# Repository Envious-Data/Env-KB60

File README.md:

# Env-KB60
 Another Raspberry Pi Pico Keyboard but this time 60% and compact!

## This project is sort of on hold kinda.

### What Dis!?

This is another Raspberry pi Pico keyboard that ive designed, its a 60% this time around and the diodes are a bit more akin to a normal keyboard, This should support ansi and ISO.
As of right now there are no mount holes nor SVGs for Laser cut acrylic, same for there being no keymap but those arent hard to make for KMK.

to add since my income is relatively low these extra boards ive made may be slow going to make progress since getting PCBs Made and acrylic made costs money which I dont have much of (basically paying bills are more important), With that said I'll happily help if you want work on your own boards of make changes to this one.

### Goal
the goal of this keyboard is to make it GH60 case compatible and a secondary objective is ANSI support.

### Extra notes
in the schematic there are double positions for some keys just to allow for ansi support since I design natively ISO first, there is also 2 backslash keys one of which can be ignored if you use ANSI or ISO.

the rpi pico will need a spacer of some sort so you'll likely just need normal male headers and snip the extra length off once you've soldered the pico to the PCB, DO NOTE that you should do this AFTER installing the switches unless you have a way of removing the rpi pico.

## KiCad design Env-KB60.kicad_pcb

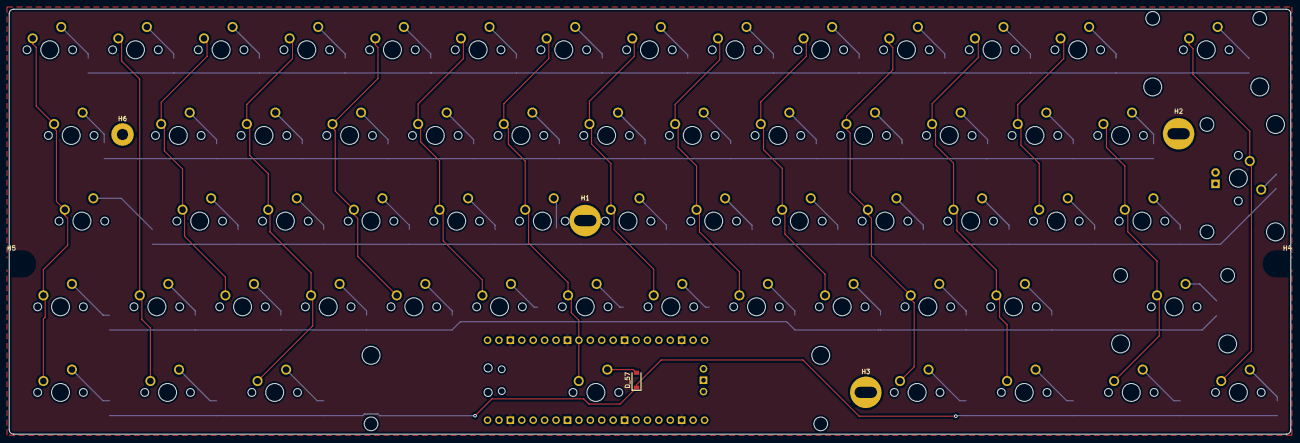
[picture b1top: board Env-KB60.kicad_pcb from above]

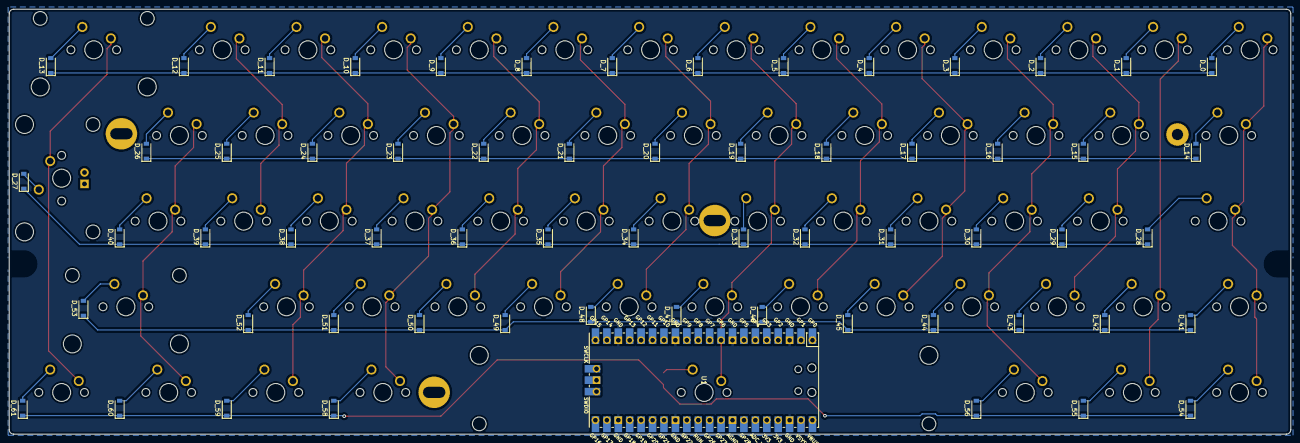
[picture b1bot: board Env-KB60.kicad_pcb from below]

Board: 2 copper layers, 285.0 x 94.5 mm, 131 parts (62 on the bottom side), 83 nets.

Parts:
D_0, D_1, D_2, D_3, D_4, D_5, D_6, D_7, D_8, D_9, D_10, D_11, D_12, D_13, D_14, D_15, D_16, D_17, D_18, D_19, D_20, D_21, D_22, D_23, D_24, D_25, D_26, D_27, D_28, D_29, D_30, D_31, D_32, D_33, D_34, D_35, D_36, D_37, D_38, D_39, D_40, D_41, D_42, D_43, D_44, D_45, D_46, D_47, D_48, D_49, D_50, D_51, D_52, D_53, D_54, D_55, D_56, D_57, D_58, D_59, D_60, D_61: D; D_SOD-123
H1, H2, H3, H4, H5, H6: MountingHole; MountingHole_2.5mm
K_0, K_1, K_2, K_3, K_4, K_5, K_6, K_7, K_8, K_9, K_10, K_11, K_12, K_15, K_16, K_17, K_18, K_19, K_20, K_21, K_22, K_23, K_24, K_25, K_26, K_29, K_30, K_31, K_32, K_33, K_34, K_35, K_36, K_37, K_38, K_39, K_40, K_42, K_43, K_44, K_45, K_46, K_47, K_48, K_49, K_50, K_51, K_52: KEYSW; MXOnly-1U-NoLED
K_13: KEYSW; MXOnly-2U-NoLED
K_14: KEYSW; MXOnly-1.5U-NoLED
K_27: KEYSW; MXOnly-ISO-ROTATED
K_28: KEYSW; MXOnly-1.75U-NoLED
K_41, K_54, K_55, K_56, K_58, K_59, K_60, K_61: KEYSW; MXOnly-1.25U-NoLED
K_53: KEYSW; MXOnly-2.75U-NoLED
K_57: KEYSW; MXOnly-6.25U-ReversedStabilizers-NoLED
U1: Pico; RPi_Pico_SMD_TH

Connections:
GND: U1.3, U1.8, U1.13, U1.18, U1.23, U1.28, U1.38
unnamed: D_0.2, K_0.2
unnamed: D_1.2, K_1.2
unnamed: D_2.2, K_2.2
unnamed: D_3.2, K_3.2
unnamed: D_4.2, K_4.2
unnamed: D_5.2, K_5.2
unnamed: D_6.2, K_6.2
unnamed: D_7.2, K_7.2
unnamed: D_8.2, K_8.2
unnamed: D_9.2, K_9.2
unnamed: D_10.2, K_10.2
unnamed: D_11.2, K_11.2
unnamed: D_12.2, K_12.2
unnamed: D_13.2, K_13.2
unnamed: D_14.2, K_14.2
unnamed: D_15.2, K_15.2
unnamed: D_16.2, K_16.2
unnamed: D_17.2, K_17.2
unnamed: D_18.2, K_18.2
unnamed: D_19.2, K_19.2
unnamed: D_20.2, K_20.2
unnamed: D_21.2, K_21.2
unnamed: D_22.2, K_22.2
unnamed: D_23.2, K_23.2
unnamed: D_24.2, K_24.2
unnamed: D_25.2, K_25.2
unnamed: D_26.2, K_26.2
unnamed: D_27.2, K_27.2
unnamed: D_28.2, K_28.2
unnamed: D_29.2, K_29.2
unnamed: D_30.2, K_30.2
unnamed: D_31.2, K_31.2
unnamed: D_32.2, K_32.2
unnamed: D_33.2, K_33.2
unnamed: D_34.2, K_34.2
unnamed: D_35.2, K_35.2
unnamed: D_36.2, K_36.2
unnamed: D_37.2, K_37.2
unnamed: D_38.2, K_38.2
unnamed: D_39.2, K_39.2
unnamed: D_40.2, K_40.2
unnamed: D_41.2, K_41.2
unnamed: D_42.2, K_42.2
unnamed: D_43.2, K_43.2
unnamed: D_44.2, K_44.2
unnamed: D_45.2, K_45.2
unnamed: D_46.2, K_46.2
unnamed: D_47.2, K_47.2
unnamed: D_48.2, K_48.2
unnamed: D_49.2, K_49.2
unnamed: D_50.2, K_50.2
unnamed: D_51.2, K_51.2
unnamed: D_52.2, K_52.2
unnamed: D_53.2, K_53.2
unnamed: D_54.2, K_54.2
unnamed: D_55.2, K_55.2
unnamed: D_56.2, K_56.2
unnamed: D_57.2, K_57.2
unnamed: D_58.2, K_58.2
unnamed: D_59.2, K_59.2
unnamed: D_60.2, K_60.2
unnamed: D_61.2, K_61.2
col0: K_0.1, K_14.1, K_28.1, K_41.1, K_54.1
col1: K_1.1, K_42.1, K_55.1
col2: K_2.1, K_15.1, K_29.1, K_43.1
col3: K_3.1, K_16.1, K_30.1, K_44.1, K_56.1
col4: K_4.1, K_17.1, K_31.1, K_45.1
col5: K_5.1, K_18.1, K_32.1, K_46.1
col6: K_6.1, K_19.1, K_33.1, K_47.1, K_57.1
col7: K_7.1, K_20.1, K_34.1, K_48.1
col8: K_8.1, K_21.1, K_35.1, K_49.1
col9: K_9.1, K_22.1, K_36.1, K_50.1
col10: K_10.1, K_23.1, K_37.1, K_51.1, K_58.1
col11: K_11.1, K_24.1, K_38.1, K_52.1, K_59.1
col12: K_12.1, K_25.1, K_39.1
col13: K_26.1, K_40.1, K_53.1, K_60.1
col14: K_13.1, K_27.1, K_61.1
row0: D_0.1, D_1.1, D_2.1, D_3.1, D_4.1, D_5.1, D_6.1, D_7.1, D_8.1, D_9.1, D_10.1, D_11.1, D_12.1, D_13.1
row1: D_14.1, D_15.1, D_16.1, D_17.1, D_18.1, D_19.1, D_20.1, D_21.1, D_22.1, D_23.1, D_24.1, D_25.1, D_26.1
row2: D_27.1, D_28.1, D_29.1, D_30.1, D_31.1, D_32.1, D_33.1, D_34.1, D_35.1, D_36.1, D_37.1, D_38.1, D_39.1, D_40.1
row3: D_41.1, D_42.1, D_43.1, D_44.1, D_45.1, D_46.1, D_47.1, D_48.1, D_49.1, D_50.1, D_51.1, D_52.1, D_53.1
row4: D_54.1, D_55.1, D_56.1, D_57.1, D_58.1, D_59.1, D_60.1, D_61.1

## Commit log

2021-04-12 Add files n stuff.
    Oh henlo, I slepy, gon sleep soon.
2021-04-13 Added 6*M2 Mount holes
    There is one mount hole in each corner and also a couple along the center line of the board, one below the space bar and the other between the top two rows.
2021-04-13 Added Gerber files + zip
2021-04-15 Idk what changed, just syncing for consistency
2021-04-22 Re-Doing this PCB
2021-04-23 Added Main trace array
2021-04-23 Added GH60 compatible mount holes.
2021-04-23 added MCU and some more traces and adjustments
